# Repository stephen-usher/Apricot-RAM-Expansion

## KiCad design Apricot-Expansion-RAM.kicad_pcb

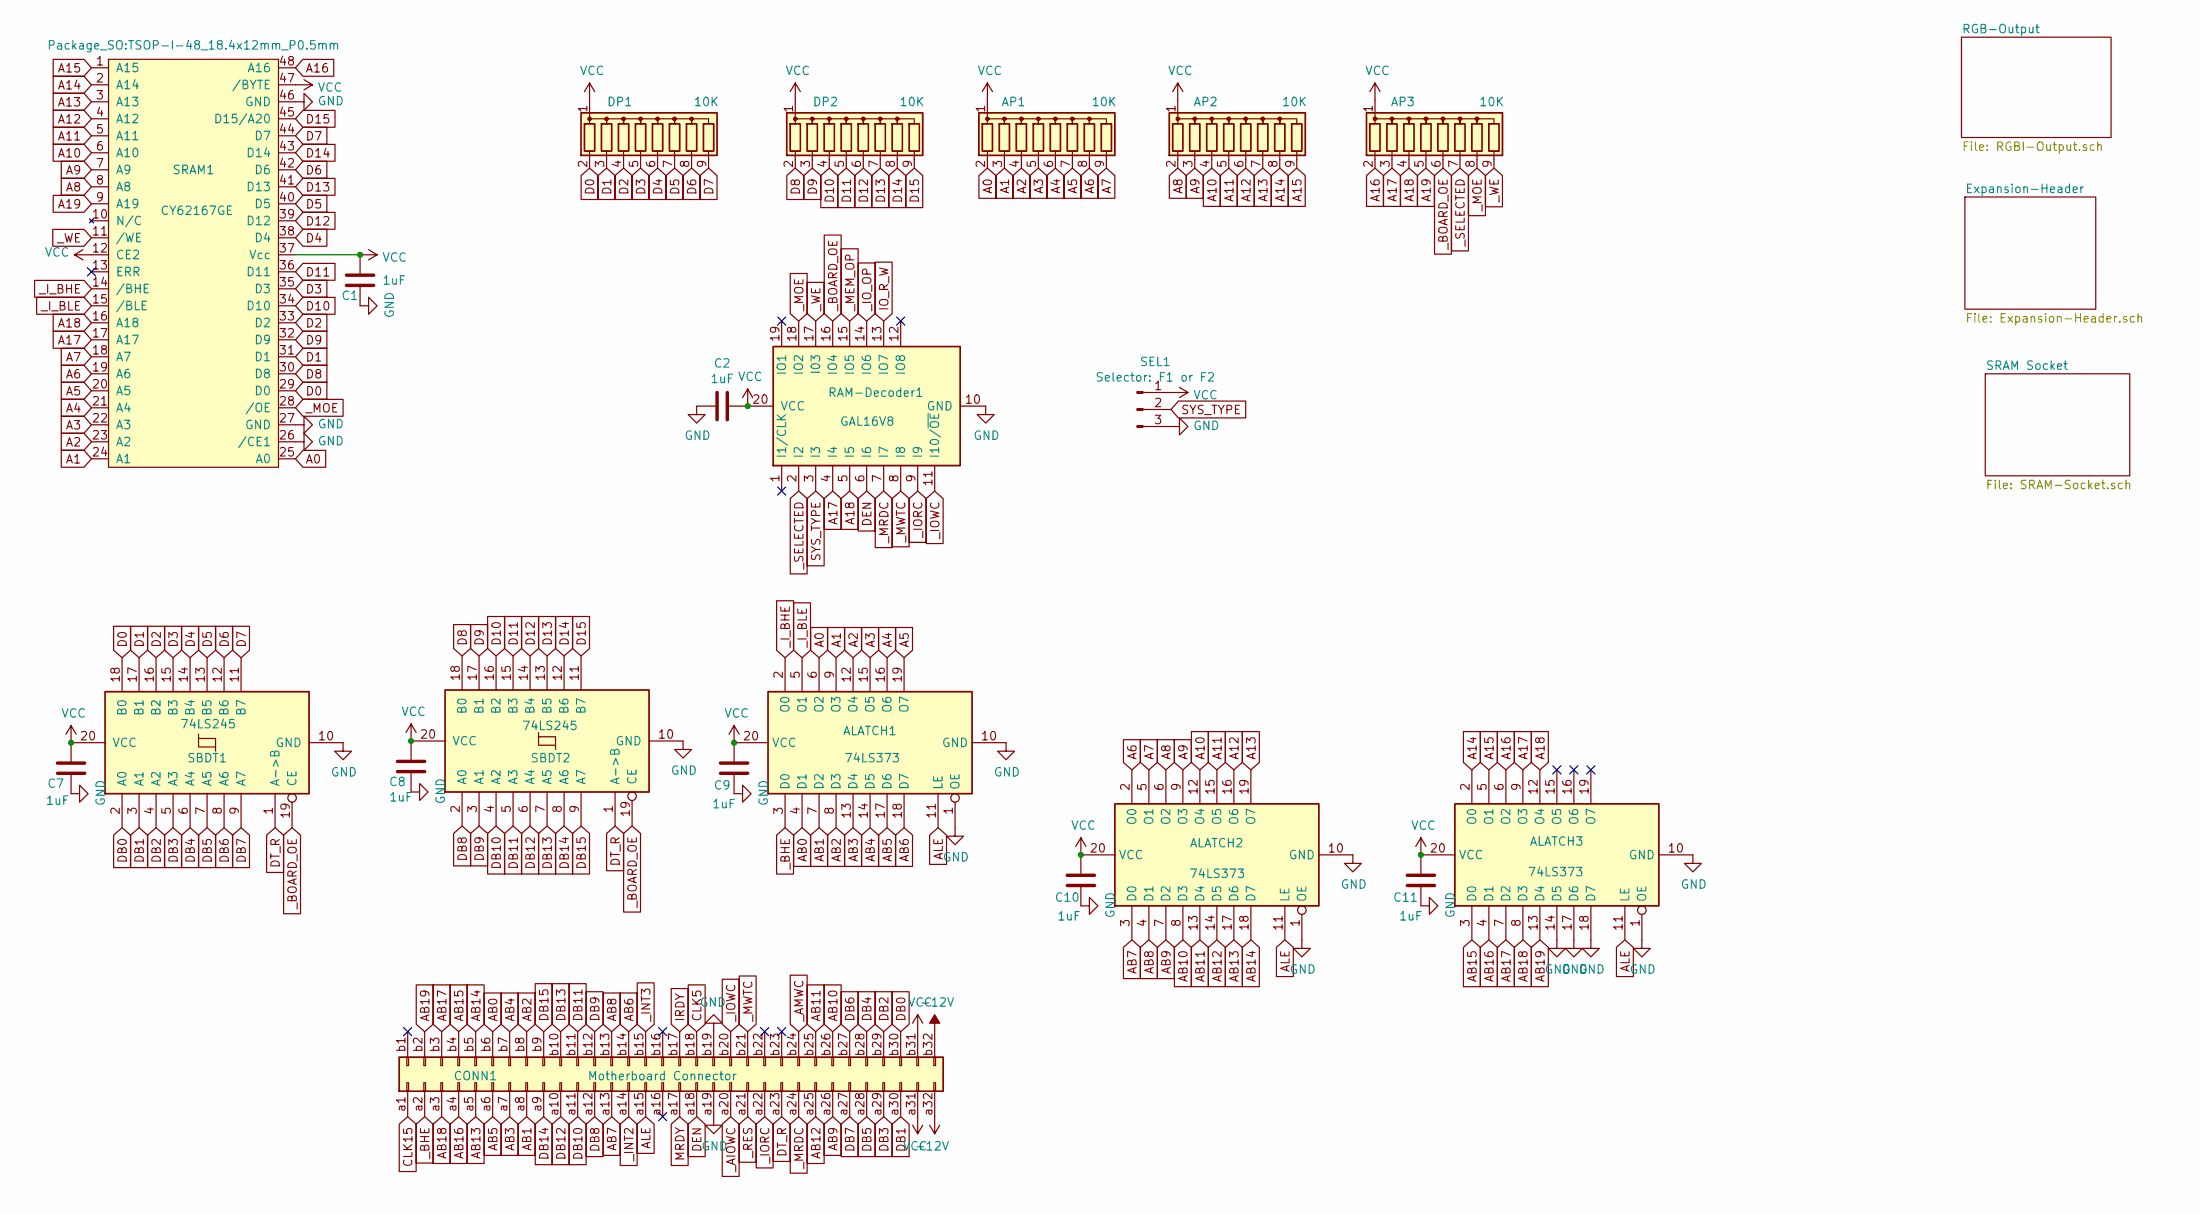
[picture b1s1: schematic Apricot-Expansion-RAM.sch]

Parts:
ALATCH1, ALATCH2, ALATCH3: 74LS373; DIP-20_W7.62mm_Socket
AP1, AP2, AP3: 10K; R_Array_SIP9
C1, C2, C7, C8, C9, C10, C11: 1uF; C_0805_2012Metric
CONN1: Motherboard Connector; DIN41612_B_2x32_Male_Horizontal_THT
DP1, DP2: 10K; R_Array_SIP9
RAM-Decoder1: GAL16V8; DIP-20_W7.62mm_Socket
SBDT1, SBDT2: 74LS245; DIP-20_W7.62mm_Socket
SEL1: Selector: F1 or F2; PinHeader_1x03_P2.54mm_Vertical
SRAM1: CY62167GE; TSOP-I-48_18.4x12mm_P0.5mm

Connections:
+12V: CONN1.a32
-12V: CONN1.b32
A0: ALATCH1.6 (O2), AP1.2 (R1), SRAM1.25 (A0); also elsewhere on the board
A1: ALATCH1.9 (O3), AP1.3 (R2), SRAM1.24 (A1); also elsewhere on the board
A2: ALATCH1.12 (O4), AP1.4 (R3), SRAM1.23 (A2); also elsewhere on the board
A3: ALATCH1.15 (O5), AP1.5 (R4), SRAM1.22 (A3); also elsewhere on the board
A4: ALATCH1.16 (O6), AP1.6 (R5), SRAM1.21 (A4); also elsewhere on the board
A5: ALATCH1.19 (O7), AP1.7 (R6), SRAM1.20 (A5); also elsewhere on the board
A6: ALATCH2.2 (O0), AP1.8 (R7), SRAM1.19 (A6); also elsewhere on the board
A7: ALATCH2.5 (O1), AP1.9 (R8), SRAM1.18 (A7); also elsewhere on the board
A8: ALATCH2.6 (O2), AP2.2 (R1), SRAM1.8 (A8); also elsewhere on the board
A9: ALATCH2.9 (O3), AP2.3 (R2), SRAM1.7 (A9); also elsewhere on the board
A10: ALATCH2.12 (O4), AP2.4 (R3), SRAM1.6 (A10); also elsewhere on the board
A11: ALATCH2.15 (O5), AP2.5 (R4), SRAM1.5 (A11); also elsewhere on the board
A12: ALATCH2.16 (O6), AP2.6 (R5), SRAM1.4 (A12); also elsewhere on the board
A13: ALATCH2.19 (O7), AP2.7 (R6), SRAM1.3 (A13); also elsewhere on the board
A14: ALATCH3.2 (O0), AP2.8 (R7), SRAM1.2 (A14); also elsewhere on the board
A15: ALATCH3.5 (O1), AP2.9 (R8), SRAM1.1 (A15); also elsewhere on the board
A16: ALATCH3.6 (O2), AP3.2 (R1), SRAM1.48 (A16); also elsewhere on the board
A17: ALATCH3.9 (O3), AP3.3 (R2), RAM-Decoder1.4 (I4), SRAM1.17 (A17); also elsewhere on the board
A18: ALATCH3.12 (O4), AP3.4 (R3), RAM-Decoder1.5 (I5), SRAM1.16 (A18); also elsewhere on the board
A19: AP3.5 (R4), SRAM1.9 (A19); also elsewhere on the board
AB0: ALATCH1.4 (D1), CONN1.b6
AB1: ALATCH1.7 (D2), CONN1.a8
AB2: ALATCH1.8 (D3), CONN1.b8
AB3: ALATCH1.13 (D4), CONN1.a7
AB4: ALATCH1.14 (D5), CONN1.b7
AB5: ALATCH1.17 (D6), CONN1.a6
AB6: ALATCH1.18 (D7), CONN1.b14
AB7: ALATCH2.3 (D0), CONN1.a13
AB8: ALATCH2.4 (D1), CONN1.b13
AB9: ALATCH2.7 (D2), CONN1.a26
AB10: ALATCH2.8 (D3), CONN1.b26
AB11: ALATCH2.13 (D4), CONN1.b25
AB12: ALATCH2.14 (D5), CONN1.a25
AB13: ALATCH2.17 (D6), CONN1.a5
AB14: ALATCH2.18 (D7), CONN1.b5
AB15: ALATCH3.3 (D0), CONN1.b4
AB16: ALATCH3.4 (D1), CONN1.a4
AB17: ALATCH3.7 (D2), CONN1.b3
AB18: ALATCH3.8 (D3), CONN1.a3
AB19: ALATCH3.13 (D4), CONN1.b2
ALE: ALATCH1.11 (LE), ALATCH2.11 (LE), ALATCH3.11 (LE), CONN1.a15
CLK5: CONN1.b18; also elsewhere on the board
CLK15: CONN1.a1; also elsewhere on the board
D0: DP1.2 (R1), SBDT1.18 (B0), SRAM1.29 (D0); also elsewhere on the board
D1: DP1.3 (R2), SBDT1.17 (B1), SRAM1.31 (D1); also elsewhere on the board
D2: DP1.4 (R3), SBDT1.16 (B2), SRAM1.33 (D2); also elsewhere on the board
D3: DP1.5 (R4), SBDT1.15 (B3), SRAM1.35 (D3); also elsewhere on the board
D4: DP1.6 (R5), SBDT1.14 (B4), SRAM1.38 (D4); also elsewhere on the board
D5: DP1.7 (R6), SBDT1.13 (B5), SRAM1.40 (D5); also elsewhere on the board
D6: DP1.8 (R7), SBDT1.12 (B6), SRAM1.42 (D6); also elsewhere on the board
D7: DP1.9 (R8), SBDT1.11 (B7), SRAM1.44 (D7); also elsewhere on the board
D8: DP2.2 (R1), SBDT2.18 (B0), SRAM1.30 (D8); also elsewhere on the board
D9: DP2.3 (R2), SBDT2.17 (B1), SRAM1.32 (D9); also elsewhere on the board
D10: DP2.4 (R3), SBDT2.16 (B2), SRAM1.34 (D10); also elsewhere on the board
D11: DP2.5 (R4), SBDT2.15 (B3), SRAM1.36 (D11); also elsewhere on the board
D12: DP2.6 (R5), SBDT2.14 (B4), SRAM1.39 (D12); also elsewhere on the board
D13: DP2.7 (R6), SBDT2.13 (B5), SRAM1.41 (D13); also elsewhere on the board
D14: DP2.8 (R7), SBDT2.12 (B6), SRAM1.43 (D14); also elsewhere on the board
D15: DP2.9 (R8), SBDT2.11 (B7), SRAM1.45 (D15/A20); also elsewhere on the board
DB0: CONN1.b30, SBDT1.2 (A0)
DB1: CONN1.a30, SBDT1.3 (A1)
DB2: CONN1.b29, SBDT1.4 (A2)
DB3: CONN1.a29, SBDT1.5 (A3)
DB4: CONN1.b28, SBDT1.6 (A4)
DB5: CONN1.a28, SBDT1.7 (A5)
DB6: CONN1.b27, SBDT1.8 (A6)
DB7: CONN1.a27, SBDT1.9 (A7)
DB8: CONN1.a12, SBDT2.2 (A0)
DB9: CONN1.b12, SBDT2.3 (A1)
DB10: CONN1.a11, SBDT2.4 (A2)
DB11: CONN1.b11, SBDT2.5 (A3)
DB12: CONN1.a10, SBDT2.6 (A4)
DB13: CONN1.b10, SBDT2.7 (A5)
DB14: CONN1.a9, SBDT2.8 (A6)
DB15: CONN1.b9, SBDT2.9 (A7)
DEN: CONN1.a18, RAM-Decoder1.6 (I6); also elsewhere on the board
DT_R: CONN1.a23, SBDT1.1 (A->B), SBDT2.1 (A->B)
GND: ALATCH1.1 (OE), ALATCH1.10 (GND), ALATCH2.1 (OE), ALATCH2.10 (GND), ALATCH3.1 (OE), ALATCH3.10 (GND), ALATCH3.14 (D5), ALATCH3.17 (D6), ALATCH3.18 (D7), C1.2, C2.2, C7.2, C8.2, C9.2, C10.2, C11.2, CONN1.a19, CONN1.b19, RAM-Decoder1.10 (GND), SBDT1.10 (GND), SBDT2.10 (GND), SEL1.3, SRAM1.26 (/CE1), SRAM1.27 (GND), SRAM1.46 (GND); also elsewhere on the board
IO_R_W: RAM-Decoder1.13 (IO7); also elsewhere on the board
IRDY: CONN1.b17; also elsewhere on the board
MRDY: CONN1.a17; also elsewhere on the board
SYS_TYPE: RAM-Decoder1.3 (I3), SEL1.2
VCC: ALATCH1.20 (VCC), ALATCH2.20 (VCC), ALATCH3.20 (VCC), AP1.1 (common), AP2.1 (common), AP3.1 (common), C1.1, C2.1, C7.1, C8.1, C9.1, C10.1, C11.1, CONN1.a31, CONN1.b31, DP1.1 (common), DP2.1 (common), RAM-Decoder1.20 (VCC), SBDT1.20 (VCC), SBDT2.20 (VCC), SEL1.1, SRAM1.12 (CE2), SRAM1.37 (Vcc), SRAM1.47 (/BYTE); also elsewhere on the board
_AIOWC: CONN1.a20; also elsewhere on the board
_AMWC: CONN1.b24; also elsewhere on the board
_BHE: ALATCH1.3 (D0), CONN1.a2
_BOARD_OE: AP3.6 (R5), RAM-Decoder1.16 (IO4), SBDT1.19 (CE), SBDT2.19 (CE)
_INT2: CONN1.a14; also elsewhere on the board
_INT3: CONN1.b15; also elsewhere on the board
_IORC: CONN1.a22, RAM-Decoder1.9 (I9)
_IOWC: CONN1.b20, RAM-Decoder1.11 (I10/~OE~)
_IO_OP: RAM-Decoder1.14 (IO6); also elsewhere on the board
_I_BHE: ALATCH1.2 (O0), SRAM1.14 (/BHE); also elsewhere on the board
_I_BLE: ALATCH1.5 (O1), SRAM1.15 (/BLE); also elsewhere on the board
_MEM_OP: RAM-Decoder1.15 (IO5); also elsewhere on the board
_MOE: AP3.8 (R7), RAM-Decoder1.18 (IO2), SRAM1.28 (/OE); also elsewhere on the board
_MRDC: CONN1.a24, RAM-Decoder1.7 (I7)
_MWTC: CONN1.b21, RAM-Decoder1.8 (I8)
_RES: CONN1.a21; also elsewhere on the board
_SELECTED: AP3.7 (R6), RAM-Decoder1.2 (I2); also elsewhere on the board
_WE: AP3.9 (R8), RAM-Decoder1.17 (I03), SRAM1.11 (/WE); also elsewhere on the board

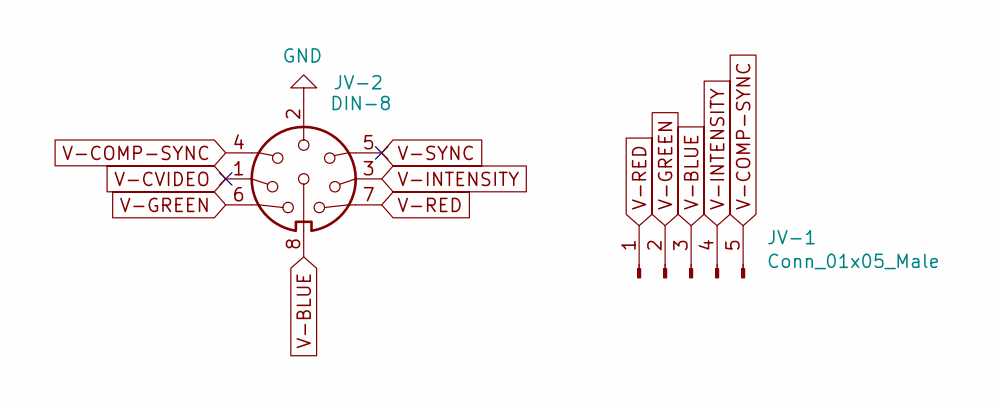
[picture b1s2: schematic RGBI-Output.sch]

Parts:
JV-1: Conn_01x05_Male; PinHeader_1x05_P2.54mm_Vertical
JV-2: DIN-8; DIN_8_PCB_Right_Angle

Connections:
GND: JV-2.2; also elsewhere on the board
V-BLUE: JV-1.3, JV-2.8
V-COMP-SYNC: JV-1.5, JV-2.4
V-CVIDEO: JV-2.1
V-GREEN: JV-1.2, JV-2.6
V-INTENSITY: JV-1.4, JV-2.3
V-RED: JV-1.1, JV-2.7
V-SYNC: JV-2.5

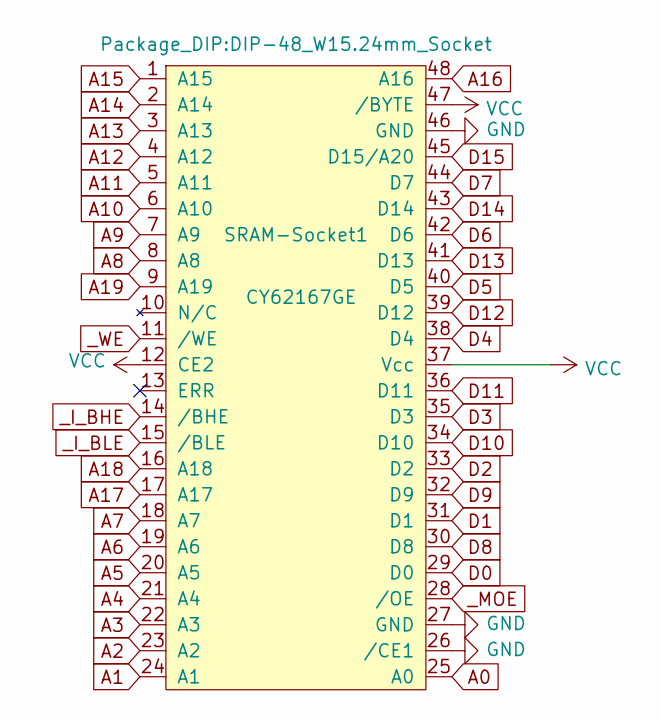
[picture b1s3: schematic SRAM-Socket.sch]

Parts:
SRAM-Socket1: CY62167GE; DIP-48_W15.24mm_Socket

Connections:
A0: SRAM-Socket1.25 (A0); also elsewhere on the board
A1: SRAM-Socket1.24 (A1); also elsewhere on the board
A2: SRAM-Socket1.23 (A2); also elsewhere on the board
A3: SRAM-Socket1.22 (A3); also elsewhere on the board
A4: SRAM-Socket1.21 (A4); also elsewhere on the board
A5: SRAM-Socket1.20 (A5); also elsewhere on the board
A6: SRAM-Socket1.19 (A6); also elsewhere on the board
A7: SRAM-Socket1.18 (A7); also elsewhere on the board
A8: SRAM-Socket1.8 (A8); also elsewhere on the board
A9: SRAM-Socket1.7 (A9); also elsewhere on the board
A10: SRAM-Socket1.6 (A10); also elsewhere on the board
A11: SRAM-Socket1.5 (A11); also elsewhere on the board
A12: SRAM-Socket1.4 (A12); also elsewhere on the board
A13: SRAM-Socket1.3 (A13); also elsewhere on the board
A14: SRAM-Socket1.2 (A14); also elsewhere on the board
A15: SRAM-Socket1.1 (A15); also elsewhere on the board
A16: SRAM-Socket1.48 (A16); also elsewhere on the board
A17: SRAM-Socket1.17 (A17); also elsewhere on the board
A18: SRAM-Socket1.16 (A18); also elsewhere on the board
A19: SRAM-Socket1.9 (A19); also elsewhere on the board
D0: SRAM-Socket1.29 (D0); also elsewhere on the board
D1: SRAM-Socket1.31 (D1); also elsewhere on the board
D2: SRAM-Socket1.33 (D2); also elsewhere on the board
D3: SRAM-Socket1.35 (D3); also elsewhere on the board
D4: SRAM-Socket1.38 (D4); also elsewhere on the board
D5: SRAM-Socket1.40 (D5); also elsewhere on the board
D6: SRAM-Socket1.42 (D6); also elsewhere on the board
D7: SRAM-Socket1.44 (D7); also elsewhere on the board
D8: SRAM-Socket1.30 (D8); also elsewhere on the board
D9: SRAM-Socket1.32 (D9); also elsewhere on the board
D10: SRAM-Socket1.34 (D10); also elsewhere on the board
D11: SRAM-Socket1.36 (D11); also elsewhere on the board
D12: SRAM-Socket1.39 (D12); also elsewhere on the board
D13: SRAM-Socket1.41 (D13); also elsewhere on the board
D14: SRAM-Socket1.43 (D14); also elsewhere on the board
D15: SRAM-Socket1.45 (D15/A20); also elsewhere on the board
GND: SRAM-Socket1.26 (/CE1), SRAM-Socket1.27 (GND), SRAM-Socket1.46 (GND); also elsewhere on the board
VCC: SRAM-Socket1.12 (CE2), SRAM-Socket1.37 (Vcc), SRAM-Socket1.47 (/BYTE); also elsewhere on the board
_I_BHE: SRAM-Socket1.14 (/BHE); also elsewhere on the board
_I_BLE: SRAM-Socket1.15 (/BLE); also elsewhere on the board
_MOE: SRAM-Socket1.28 (/OE); also elsewhere on the board
_WE: SRAM-Socket1.11 (/WE); also elsewhere on the board

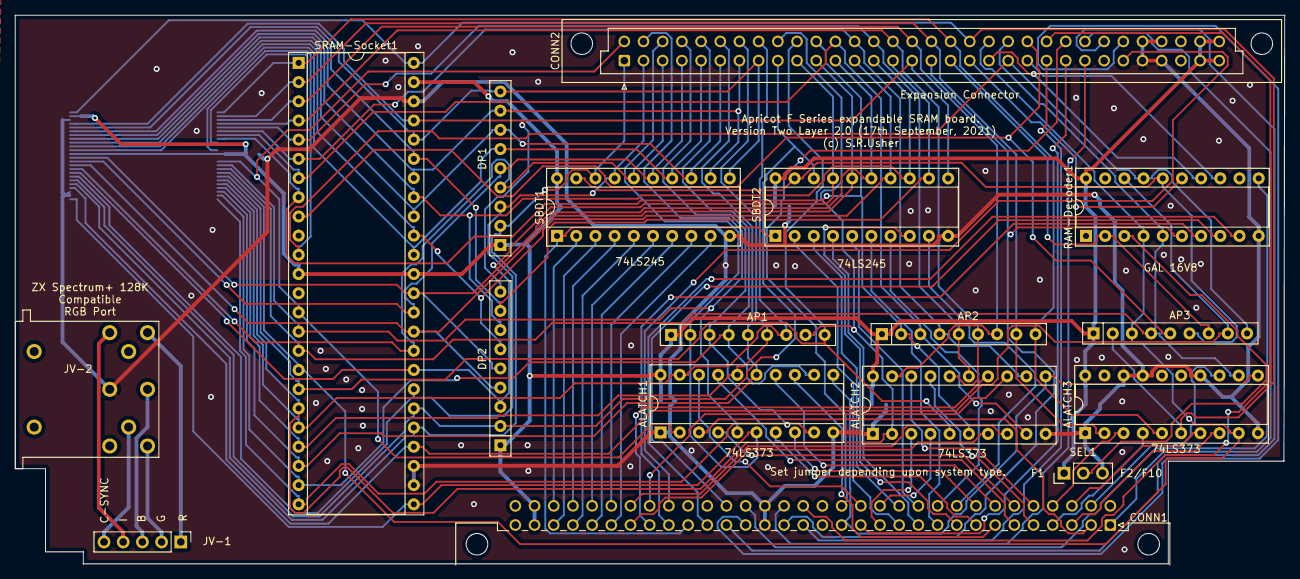
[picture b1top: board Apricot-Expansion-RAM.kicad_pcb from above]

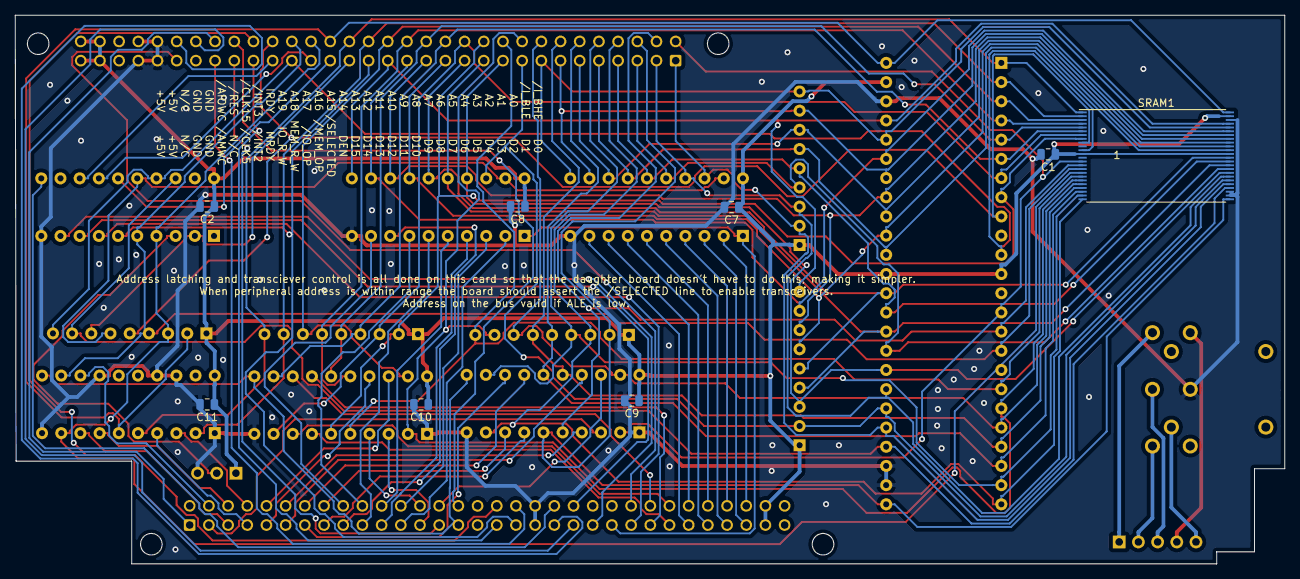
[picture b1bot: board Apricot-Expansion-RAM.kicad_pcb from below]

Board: 2 copper layers, 168.0 x 72.6 mm, 25 parts (8 on the bottom side), 106 nets.

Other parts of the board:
CONN2: Expansion; DIN41612_B_2x32_Female_Vertical_THT

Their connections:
A0: CONN2.b3; also elsewhere on the board
A1: CONN2.b4; also elsewhere on the board
A2: CONN2.b5; also elsewhere on the board
A3: CONN2.b6; also elsewhere on the board
A4: CONN2.b7; also elsewhere on the board
A5: CONN2.b8; also elsewhere on the board
A6: CONN2.b9; also elsewhere on the board
A7: CONN2.b10; also elsewhere on the board
A8: CONN2.b11; also elsewhere on the board
A9: CONN2.b12; also elsewhere on the board
A10: CONN2.b13; also elsewhere on the board
A11: CONN2.b14; also elsewhere on the board
A12: CONN2.b15; also elsewhere on the board
A13: CONN2.b16; also elsewhere on the board
A14: CONN2.b17; also elsewhere on the board
A15: CONN2.b18; also elsewhere on the board
A16: CONN2.b19; also elsewhere on the board
A17: CONN2.b20; also elsewhere on the board
A18: CONN2.b21; also elsewhere on the board
A19: CONN2.b22; also elsewhere on the board
CLK5: CONN2.a25; also elsewhere on the board
CLK15: CONN2.b25; also elsewhere on the board
D0: CONN2.a1; also elsewhere on the board
D1: CONN2.a2; also elsewhere on the board
D2: CONN2.a3; also elsewhere on the board
D3: CONN2.a4; also elsewhere on the board
D4: CONN2.a5; also elsewhere on the board
D5: CONN2.a6; also elsewhere on the board
D6: CONN2.a7; also elsewhere on the board
D7: CONN2.a8; also elsewhere on the board
D8: CONN2.a9; also elsewhere on the board
D9: CONN2.a10; also elsewhere on the board
D10: CONN2.a11; also elsewhere on the board
D11: CONN2.a12; also elsewhere on the board
D12: CONN2.a13; also elsewhere on the board
D13: CONN2.a14; also elsewhere on the board
D14: CONN2.a15; also elsewhere on the board
D15: CONN2.a16; also elsewhere on the board
DEN: CONN2.a17; also elsewhere on the board
GND: CONN2.a28, CONN2.a29, CONN2.b28, CONN2.b29; also elsewhere on the board
IO_R_W: CONN2.a22; also elsewhere on the board
IRDY: CONN2.b23; also elsewhere on the board
MRDY: CONN2.a23; also elsewhere on the board
VCC: CONN2.a31, CONN2.a32, CONN2.b31, CONN2.b32; also elsewhere on the board
_AIOWC: CONN2.b27; also elsewhere on the board
_AMWC: CONN2.a27; also elsewhere on the board
_INT2: CONN2.a24; also elsewhere on the board
_INT3: CONN2.b24; also elsewhere on the board
_IO_OP: CONN2.a20; also elsewhere on the board
_I_BHE: CONN2.b1; also elsewhere on the board
_I_BLE: CONN2.b2; also elsewhere on the board
_MEM_OP: CONN2.a19; also elsewhere on the board
_RES: CONN2.b26; also elsewhere on the board
_SELECTED: CONN2.a18; also elsewhere on the board
_WE: CONN2.a21; also elsewhere on the board
